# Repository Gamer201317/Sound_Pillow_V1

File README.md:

# Sound_Pillow_V1

Sound Pillow is an 12 key sounboard with aa rotarty encoder 7 sk mini-e and uses kmk firmware

Features:

12 keys
EC11 Rotary encoder for Volume
7 sk mini-e for a little disco
and aa case in the shape of a pillow 

Cad Model:

the case uses glue to fit everything together at the final stage 
it haas 2 sepaaretly printed pieces the bottom where the pcb slides in to and one top hat you put ovr your key

make in Tinkercad becausee fusion 360 was to difucult 

Pcb:

Here's my PCB! It was made in KiCad. The silkscreen i found on the internet and aded it 

this is the schematic

and this is the pcb

and the next time i'm doing something like this i would like to cleaan the schematic up a little bit more

Firmware Overview

This hackpad uses kmk firmware for everything 
the rotary encoder changes thee volume and i didn't use the button
The 12 keys act as f13-f24 and i use https://www.voicemod.net/ as the software  so i can use the macropad as a soundboard  in discord 
and the leds are there for a little disco

Bom 

-12x Cherry MX Switches
12x DSA Keycaps
-2x M3x16mm SHCS Bolts
-5x 1N4148 DO-35 Diodes.
-7x sk mini-e LEDs
-1x EC11 Rotary Encoder
-1x XIAO RP2040
-1x Case (2 printed parts)

and if you're wondering why there is a hole in the top right of the case that's so you can add an acrylic plate or just watch the components

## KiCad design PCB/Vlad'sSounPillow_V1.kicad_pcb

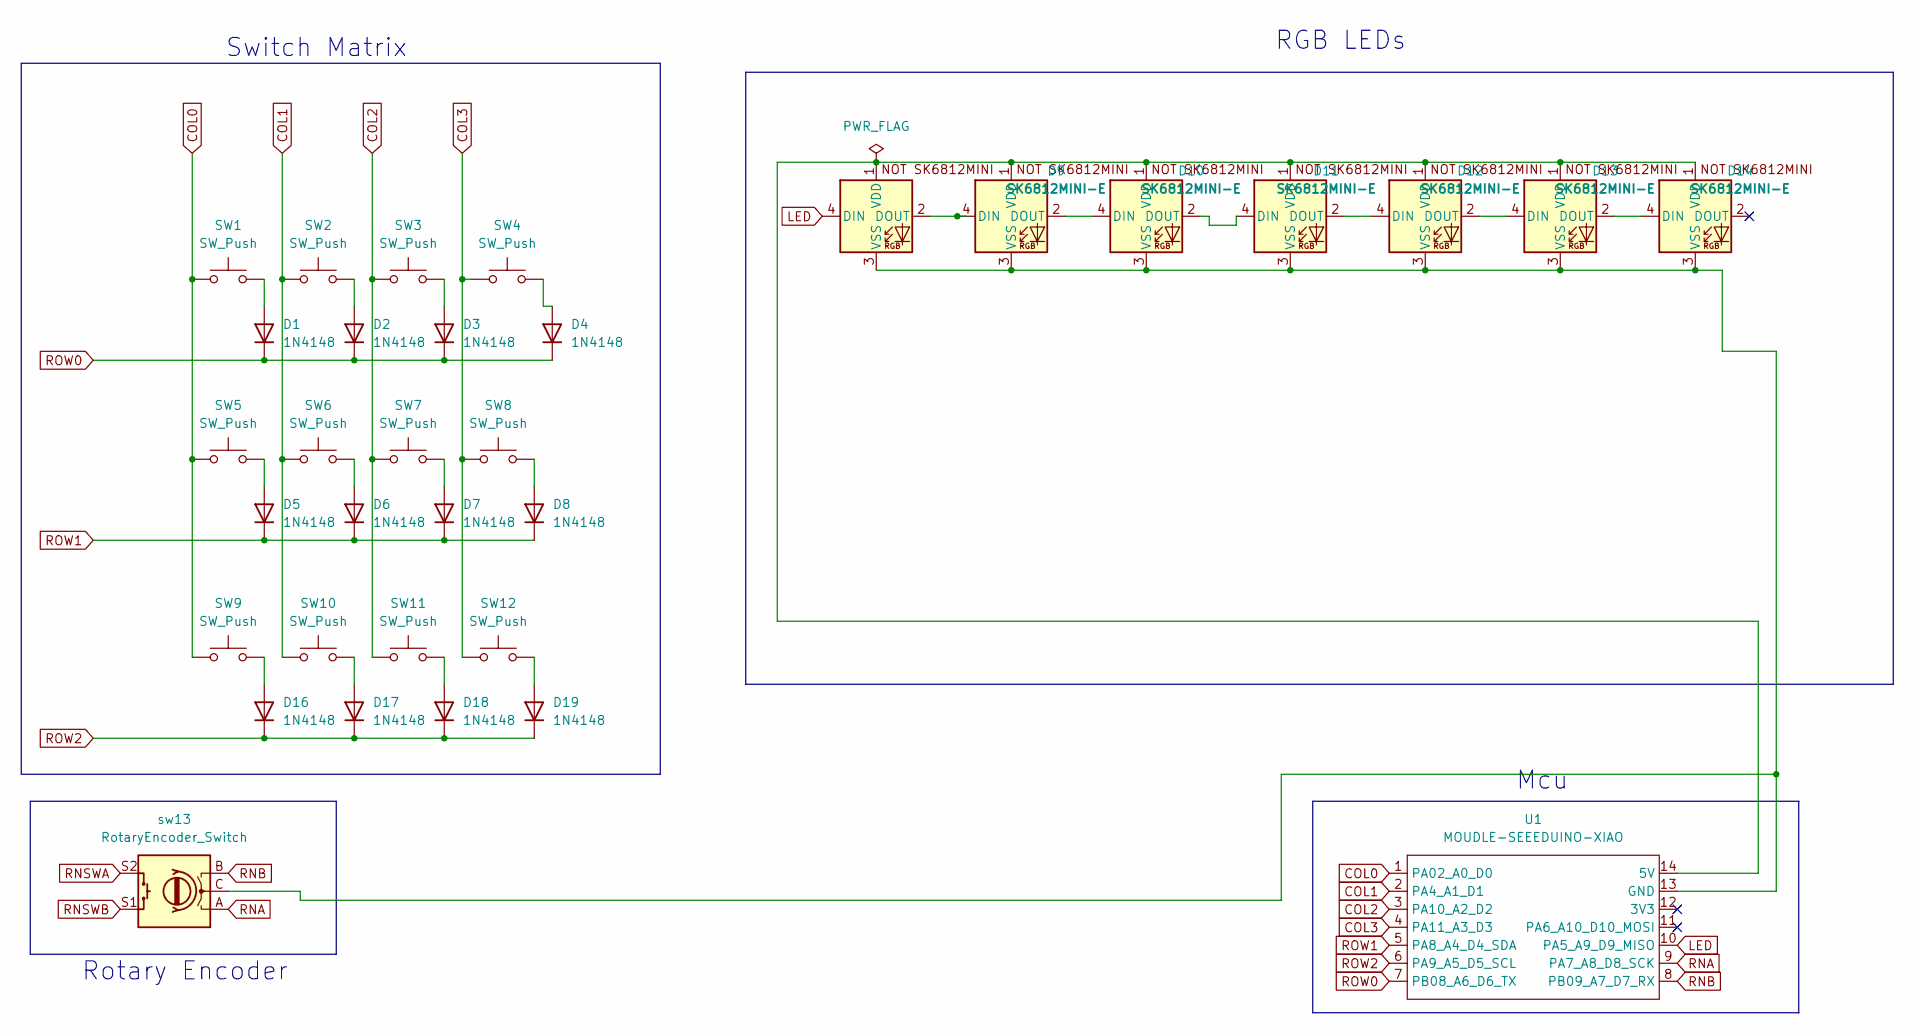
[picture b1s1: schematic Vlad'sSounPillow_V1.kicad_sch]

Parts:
D1, D2, D3, D4, D5, D6, D7, D8, D16, D17, D18, D19: 1N4148; D_DO-35_SOD27_P7.62mm_Horizontal
D9, D10, D11, D12, D13, D14, D15: SK6812MINI-E; SK6812MINI-E_fixed
SW1, SW2, SW3, SW4, SW5, SW6, SW7, SW8, SW9, SW10, SW11, SW12: SW_Push; SW_Cherry_MX_1.00u_PCB
U1: MOUDLE-SEEEDUINO-XIAO; XIAO-Generic-Hybrid-14P-2.54-21X17.8MM
sw13: RotaryEncoder_Switch; RotaryEncoder_Alps_EC11E-Switch_Vertical_H20mm

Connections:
COL0: SW1.1, SW5.1, SW9.1, U1.1 (PA02_A0_D0)
COL1: SW2.1, SW6.1, SW10.1, U1.2 (PA4_A1_D1)
COL2: SW3.1, SW7.1, SW11.1, U1.3 (PA10_A2_D2)
COL3: SW4.1, SW8.1, SW12.1, U1.4 (PA11_A3_D3)
LED: D9.4 (DIN), U1.10 (PA5_A9_D9_MISO)
unnamed: D1.2 (A), SW1.2
unnamed: D2.2 (A), SW2.2
unnamed: D3.2 (A), SW3.2
unnamed: D4.2 (A), SW4.2
unnamed: D5.2 (A), SW5.2
unnamed: D6.2 (A), SW6.2
unnamed: D7.2 (A), SW7.2
unnamed: D8.2 (A), SW8.2
unnamed: D9.2 (DOUT), D10.4 (DIN)
unnamed: D10.2 (DOUT), D11.4 (DIN)
unnamed: D9.1 (VDD), D10.1 (VDD), D11.1 (VDD), D12.1 (VDD), D13.1 (VDD), D14.1 (VDD), D15.1 (VDD), U1.14 (5V)
unnamed: D9.3 (VSS), D10.3 (VSS), D11.3 (VSS), D12.3 (VSS), D13.3 (VSS), D14.3 (VSS), D15.3 (VSS), U1.13 (GND), sw13.C
unnamed: D11.2 (DOUT), D12.4 (DIN)
unnamed: D12.2 (DOUT), D13.4 (DIN)
unnamed: D13.2 (DOUT), D14.4 (DIN)
unnamed: D14.2 (DOUT), D15.4 (DIN)
unnamed: D16.2 (A), SW9.2
unnamed: D17.2 (A), SW10.2
unnamed: D18.2 (A), SW11.2
unnamed: D19.2 (A), SW12.2
RNA: U1.9 (PA7_A8_D8_SCK), sw13.A
RNB: U1.8 (PB09_A7_D7_RX), sw13.B
RNSWA: sw13.S2
RNSWB: sw13.S1
ROW0: D1.1 (K), D2.1 (K), D3.1 (K), D4.1 (K), U1.7 (PB08_A6_D6_TX)
ROW1: D5.1 (K), D6.1 (K), D7.1 (K), D8.1 (K), U1.5 (PA8_A4_D4_SDA)
ROW2: D16.1 (K), D17.1 (K), D18.1 (K), D19.1 (K), U1.6 (PA9_A5_D5_SCL)

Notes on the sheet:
RGB LEDs
Switch Matrix
Mcu
Rotary Encoder

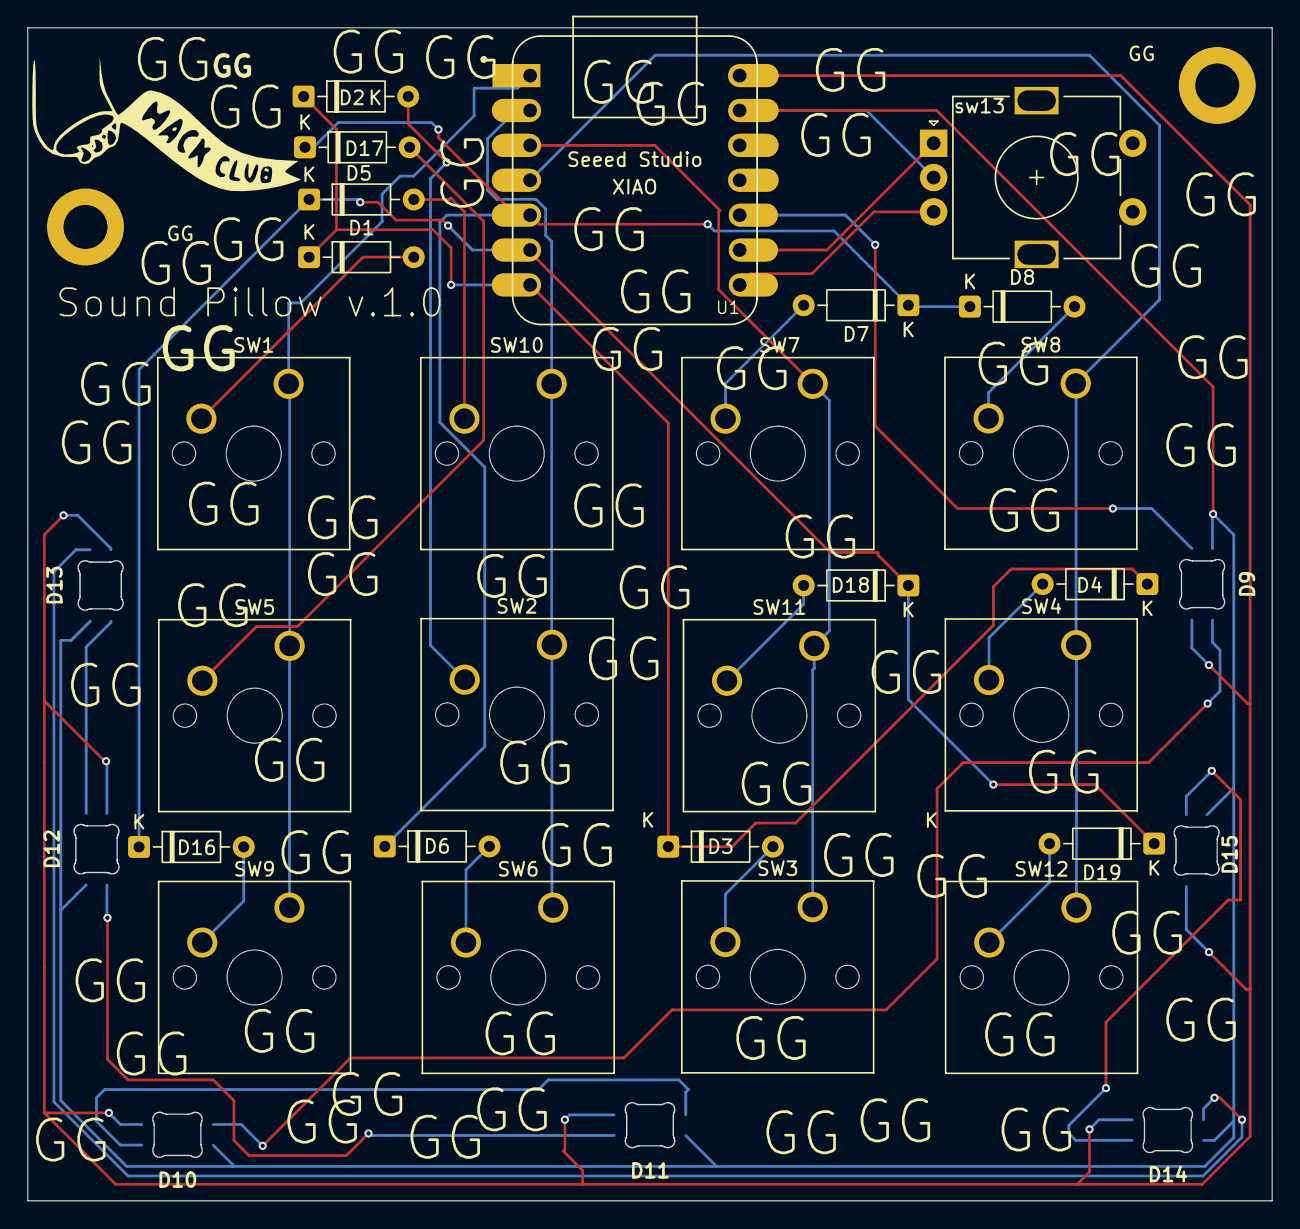
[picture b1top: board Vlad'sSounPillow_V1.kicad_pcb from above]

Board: 2 copper layers, 90.6 x 85.4 mm, 36 parts (0 on the bottom side), 30 nets.

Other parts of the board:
GG: M3 screw; MountingHole_3.2mm_M3_DIN965_Pad
GG#2: LOGO
GG#3: M3 screw; MountingHole_3.2mm_M3_DIN965_Pad
